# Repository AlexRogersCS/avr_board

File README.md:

# AVR Development Board

I like to explore different instruction sets during my Computer Architecture course - typically x86-64, ARMv7, ARMv8 and AVR. For the latter, I thought it would be fun to have a small cheap development board that the students could experiment with, so I designed one.

The board uses an 8-bit Atmel AT90USB162 processor since it requires minimal external components, comes with a factory programmed USB bootloader so no additional programmer is required, and can implement USB devices such as single key keyboards and mice.

This repository contains the Eagle CAD, Gerber and placement files, along with the BOM and a couple of simple code examples that use AVR-GCC and Gerd’s AVR assembler ([gavrasm](http://www.avr-asm-tutorial.net/gavrasm/index_en.html)).

## Development Tools

The AVR-GCC developnment tools and the programmer can be installed as below:

On Ubuntu 20.04 LTS

```
> sudo apt-get install libusb
> sudo apt-get install dfu-programmer
> sudo apt-get install gcc-avr binutils-avr avr-libc
```

On Fedora 32

```
> sudo dnf install libusb
> sudo dnf install dfu-programmer
> sudo dnf install avr-gcc avr-binutils avr-libc
```

Gerd’s AVR assembler is a simple assembler that generate hex files directly. It supports many AVR processors, including the AT90USB162, without requiring any additional configuration files. It can be installed from [here](http://www.avr-asm-tutorial.net/gavrasm/index_en.html).

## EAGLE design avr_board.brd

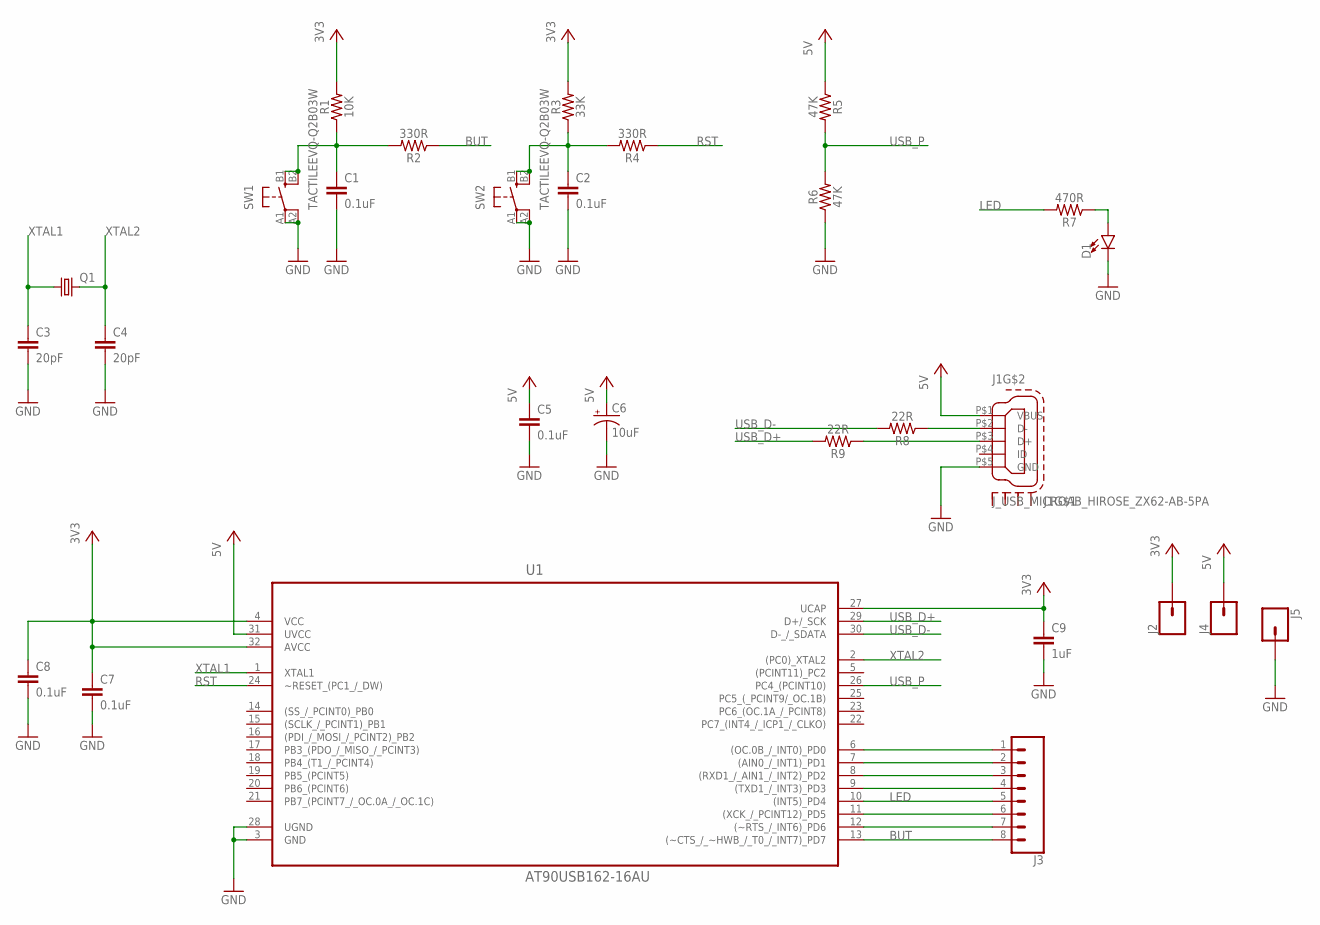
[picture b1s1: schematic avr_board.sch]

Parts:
C1, C2, C5, C7, C8: 0.1uF; 0603
C3, C4: 20pF; 0603
C6: 10uF; EIA3216
C9: 1uF; 0603
D1: LEDPLCC; PLCC-2
J1: J_USB_MICROAB_HIROSE_ZX62-AB-5PA
J2, J4, J5: CONN_01; 1X01
J3: CONN_08"; 1X08
Q1: CRYSTALCTS406; CTS406
R1: 10K; 0603
R2, R4: 330R; 0603
R3: 33K; 0603
R5, R6: 47K; 0603
R7: 470R; 0603
R8, R9: 22R; 0603
SW1, SW2: TACTILEEVQ-Q2B03W; TACTILE_PAC
U1: AT90USB162-16AU; QFP80P900X900X120-32N

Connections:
+5V: C5.1, C6.A (+), J1.P$1 (VBUS), J4.1, R5.1, U1.31 (UVCC)
BUT: J3.8, R2.1, U1.13 ((~CTS_/_~HWB_/_T0_/_INT7)_PD7)
GND: C1.2, C2.2, C3.2, C4.2, C5.2, C6.C (-), C7.2, C8.2, C9.2, D1.C, J1.P$5 (GND), J5.1, R6.1, SW1.A1, SW1.A2, SW2.A1, SW2.A2, U1.3 (GND), U1.28 (UGND)
LED: J3.5, R7.2, U1.10 ((INT5)_PD4)
unnamed: C1.1, R1.1, R2.2, SW1.B1, SW1.B2
unnamed: D1.A, R7.1
unnamed: C2.1, R3.1, R4.2, SW2.B1, SW2.B2
unnamed: J3.7, U1.12 ((~RTS_/_INT6)_PD6)
unnamed: J1.P$2 (D-), R8.1
unnamed: J1.P$3 (D+), R9.1
unnamed: J3.6, U1.11 ((XCK_/_PCINT12)_PD5)
unnamed: J3.4, U1.9 ((TXD1_/_INT3)_PD3)
unnamed: J3.3, U1.8 ((RXD1_/_AIN1_/_INT2)_PD2)
unnamed: J3.2, U1.7 ((AIN0_/_INT1)_PD1)
unnamed: J3.1, U1.6 ((OC.0B_/_INT0)_PD0)
RST: R4.1, U1.24 (~RESET_(PC1_/_DW))
USB_D+: R9.2, U1.29 (D+/_SCK)
USB_D-: R8.2, U1.30 (D-_/_SDATA)
USB_P: R5.2, R6.2, U1.26 (PC4_(PCINT10))
VCC: C7.1, C8.1, C9.1, J2.1, R1.2, R3.2, U1.4 (VCC), U1.27 (UCAP), U1.32 (AVCC)
XTAL1: C3.1, Q1.1, U1.1 (XTAL1)
XTAL2: C4.1, Q1.3 (2), U1.2 ((PC0)_XTAL2)

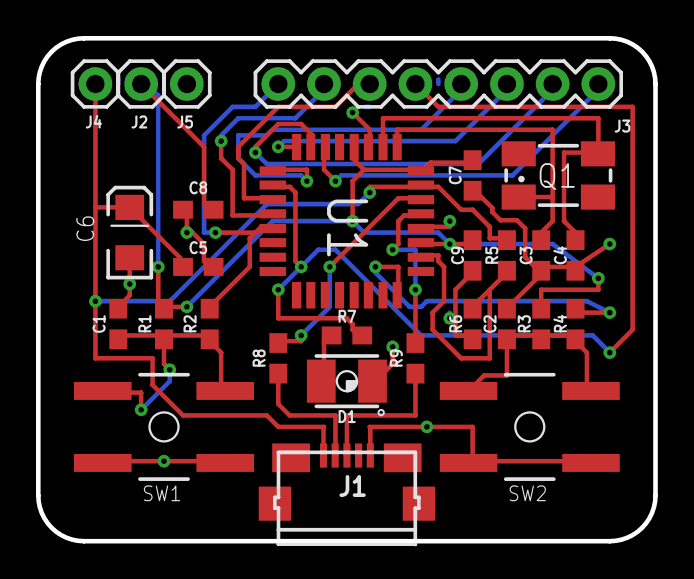
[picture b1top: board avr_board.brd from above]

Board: 2 copper layers, 34.3 x 27.9 mm, 28 parts (0 on the bottom side), 22 nets.

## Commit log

2021-03-13 Initial commit.
2021-03-13 Add code examples.
2021-03-14 Add Gerbers.
2021-03-14 Add schematic.
2021-03-14 Add photo.

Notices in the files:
parts and their libraries:
SparkFun-Resistors: Licensing: Creative Commons ShareAlike 4.0 International - https://creativecommons.org/licenses/by-sa/4.0
